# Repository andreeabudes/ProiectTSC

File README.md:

## Proiect InkTime

## Diagrama Bloc
Sistemul este organizat in jurul microcontroller-ului nRF52840, care gestioneaza comunicarea Bluetooth, procesarea datelor de la senzori si controlul afisajului.

## BOM (Bill Of Materials)
| Component | Part Number | Package | Function | Datasheet |
|---|---|---|---|---|
| MCU | nRF52840-QIAA-R | aQFN73 (7x7) | Microcontroller + BLE + USB | [Datasheet](https://docs.nordicsemi.com/) |
| Charger / Power Path | BQ25180YBGR | DSBGA-8 | Li-Ion/LiPo charger with power path | [Datasheet](https://www.ti.com/lit/ds/symlink/bq25180.pdf) |
| Buck-Boost Regulator | RT6160AWSC | WLCSP-15 | 3.3V system rail regulator | [Datasheet](https://www.richtek.com/assets/product_file/RT6160A/DS6160A-05.pdf) |
| Fuel Gauge | MAX17048G+T10 | DFN-8 (2x2) | Battery SOC monitoring | [Datasheet](https://www.analog.com/media/en/technical-documentation/data-sheets/MAX17048-MAX17049.pdf) |
| Accelerometer | BMA421 | LGA-12 (2x2) | Step counting + motion wake | [Datasheet](https://jlcpcb.com/partdetail/Bosch_Sensortec-BMA421/C5242966) |
| Haptic Driver | DRV2605LDGSR | VSSOP-10 | ERM motor driver with effects library | [Datasheet](https://www.ti.com/lit/ds/symlink/drv2605l.pdf) |
| PFET (EPD power) | SI2301CDS | SOT-23 | E-paper display power gating | [Datasheet](https://jlcpcb.com/partdetail/Changjiang_Electronics_Tech_CJ-SI2301CDS/C10487) |
| USB ESD Protection | USBLC6-2SC6Y | SOT-23-6 | ESD protection on USB data lines | [Datasheet](https://www.st.com/resource/en/datasheet/usblc6-2.pdf) |
| USB Type-C Connector | KH-TYPE-C-16P | 16-pin SMD | USB charging + data | [Datasheet](https://www.google.com/search?q=%23) |
 
> Toate rezistentele folosite sunt in capsula **0201**. Condensatoarele de bypass/decuplare de **100nF** sunt **0201**, iar cele care depasesc **100nF** sunt **0402**, conform constrangerilor de design.

## Functionalitate Hardware

### Module si Senzori

- **MCU – nRF52840:** Ales pentru consumul redus de energie si capabilitatile Bluetooth Low Energy (BLE). Acesta gestioneaza protocolul SPI pentru ecran, I2C pentru senzori si controleaza starea sistemului.

- **Display E-Paper:** Ofera o lizibilitate excelenta in lumina soarelui si consuma energie doar in momentul refresh-ului, fiind ideal pentru un smartwatch unde autonomia bateriei este critica.

- **Management Putere:** Sistem de power path si incarcare cu BQ25180YBGR, impreuna cu regulatorul Buck-Boost RT6160AWSC care asigura o tensiune stabila de 3.3V, indiferent de nivelul de descarcare al bateriei Li-Po. Monitorizarea precisa a bateriei (SOC) este realizata de integratul MAX17048G+T10.

- **Senzor Miscare:** Accelerometrul BMA421 este folosit pentru detectarea miscarii mainii (ex: "lift-to-wake" pentru a trezi ecranul din sleep) si pentru aplicatii de tip pedometru (step counting).

- **Feedback Haptic:** Motorul ERM este controlat precis de driverul DRV2605LDGSR, care include o librarie interna de efecte haptice.

---

### Specificatii Comunicatie

- **SPI (Display):** Interfata rapida pentru a asigura un refresh optim al ecranului (semnale MOSI, SCK, CS, DC).

- **I2C (Senzori & Power):** Folosita pentru comunicarea cu accelerometrul, fuel gauge-ul, charger-ul si driverul haptic.

- **SWD (Serial Wire Debug):** Interfata hardware standard de la ARM, conectata la un conector TC2030, folosita pentru incarcarea codului pe placa si pentru depanare pas cu pas a software-ului.

---

## Descriere pini nRF52840  

| Pin | Descriere |
|-----|----------|
| VDD | Alimentare 3V3 |
| DCC | Power regulation |
| DEC4 | Power regulation |
| VSS | GND |
| P0.02 / AIN0 | SPI SCK (clock pentru display) |
| P0.02 / AIN0 | SPI MOSI (master output slave in) |
| DEC2 | GND, power regulation |
| VDD | Alimentare 3V3 |
| XC2, XC1 | Oscilator X1 (32 MHz) |
| DEC3 | GND |
| DEC6 | Power regulation |
| VSS_PA | Alimentare antenă |
| ANT | Conectare antenă |
| P0.10 / NFC2 | Semnal alertă baterie (Fuel Gauge) |
| DEC5 | GND, power regulation |
| P1.02 | Buton Down |
| P1.01 | Control alimentare display |
| SWDIO, SWDCLK | Programare și debug |
| VDD | Alimentare 3V3 |
| VSS_PAD | GND |
| P1.00 | SWO (debug) |
| P0.18 / RESET | Pin Reset |
| P0.17, P0.16, P0.15 | Interfață display |
| P0.13, P0.14 | Butoane Enter / Up |
| D-, D+ | USB (transmisie diferențială) |
| VBUS | Alimentare USB 5V |
| DEC3V3 | GND (intern, power regulation) |
| DCCH | Nefolosit |
| VDDH, VDD | Alimentare 3V3 |
| P0.12 | Enable driver haptic |
| P0.11 | Alertă alimentare (de la LiPo Charger) |
| P1.08, P0.08 | Interrupții IMU |
| P0.07, P0.06 | I2C (SCL, SDA) |
| P0.05 / AIN3 | Chip Select display |
| XL2, XL1 | Oscilator X2 (32 kHz) |
| DEC1 | GND, power regulation |

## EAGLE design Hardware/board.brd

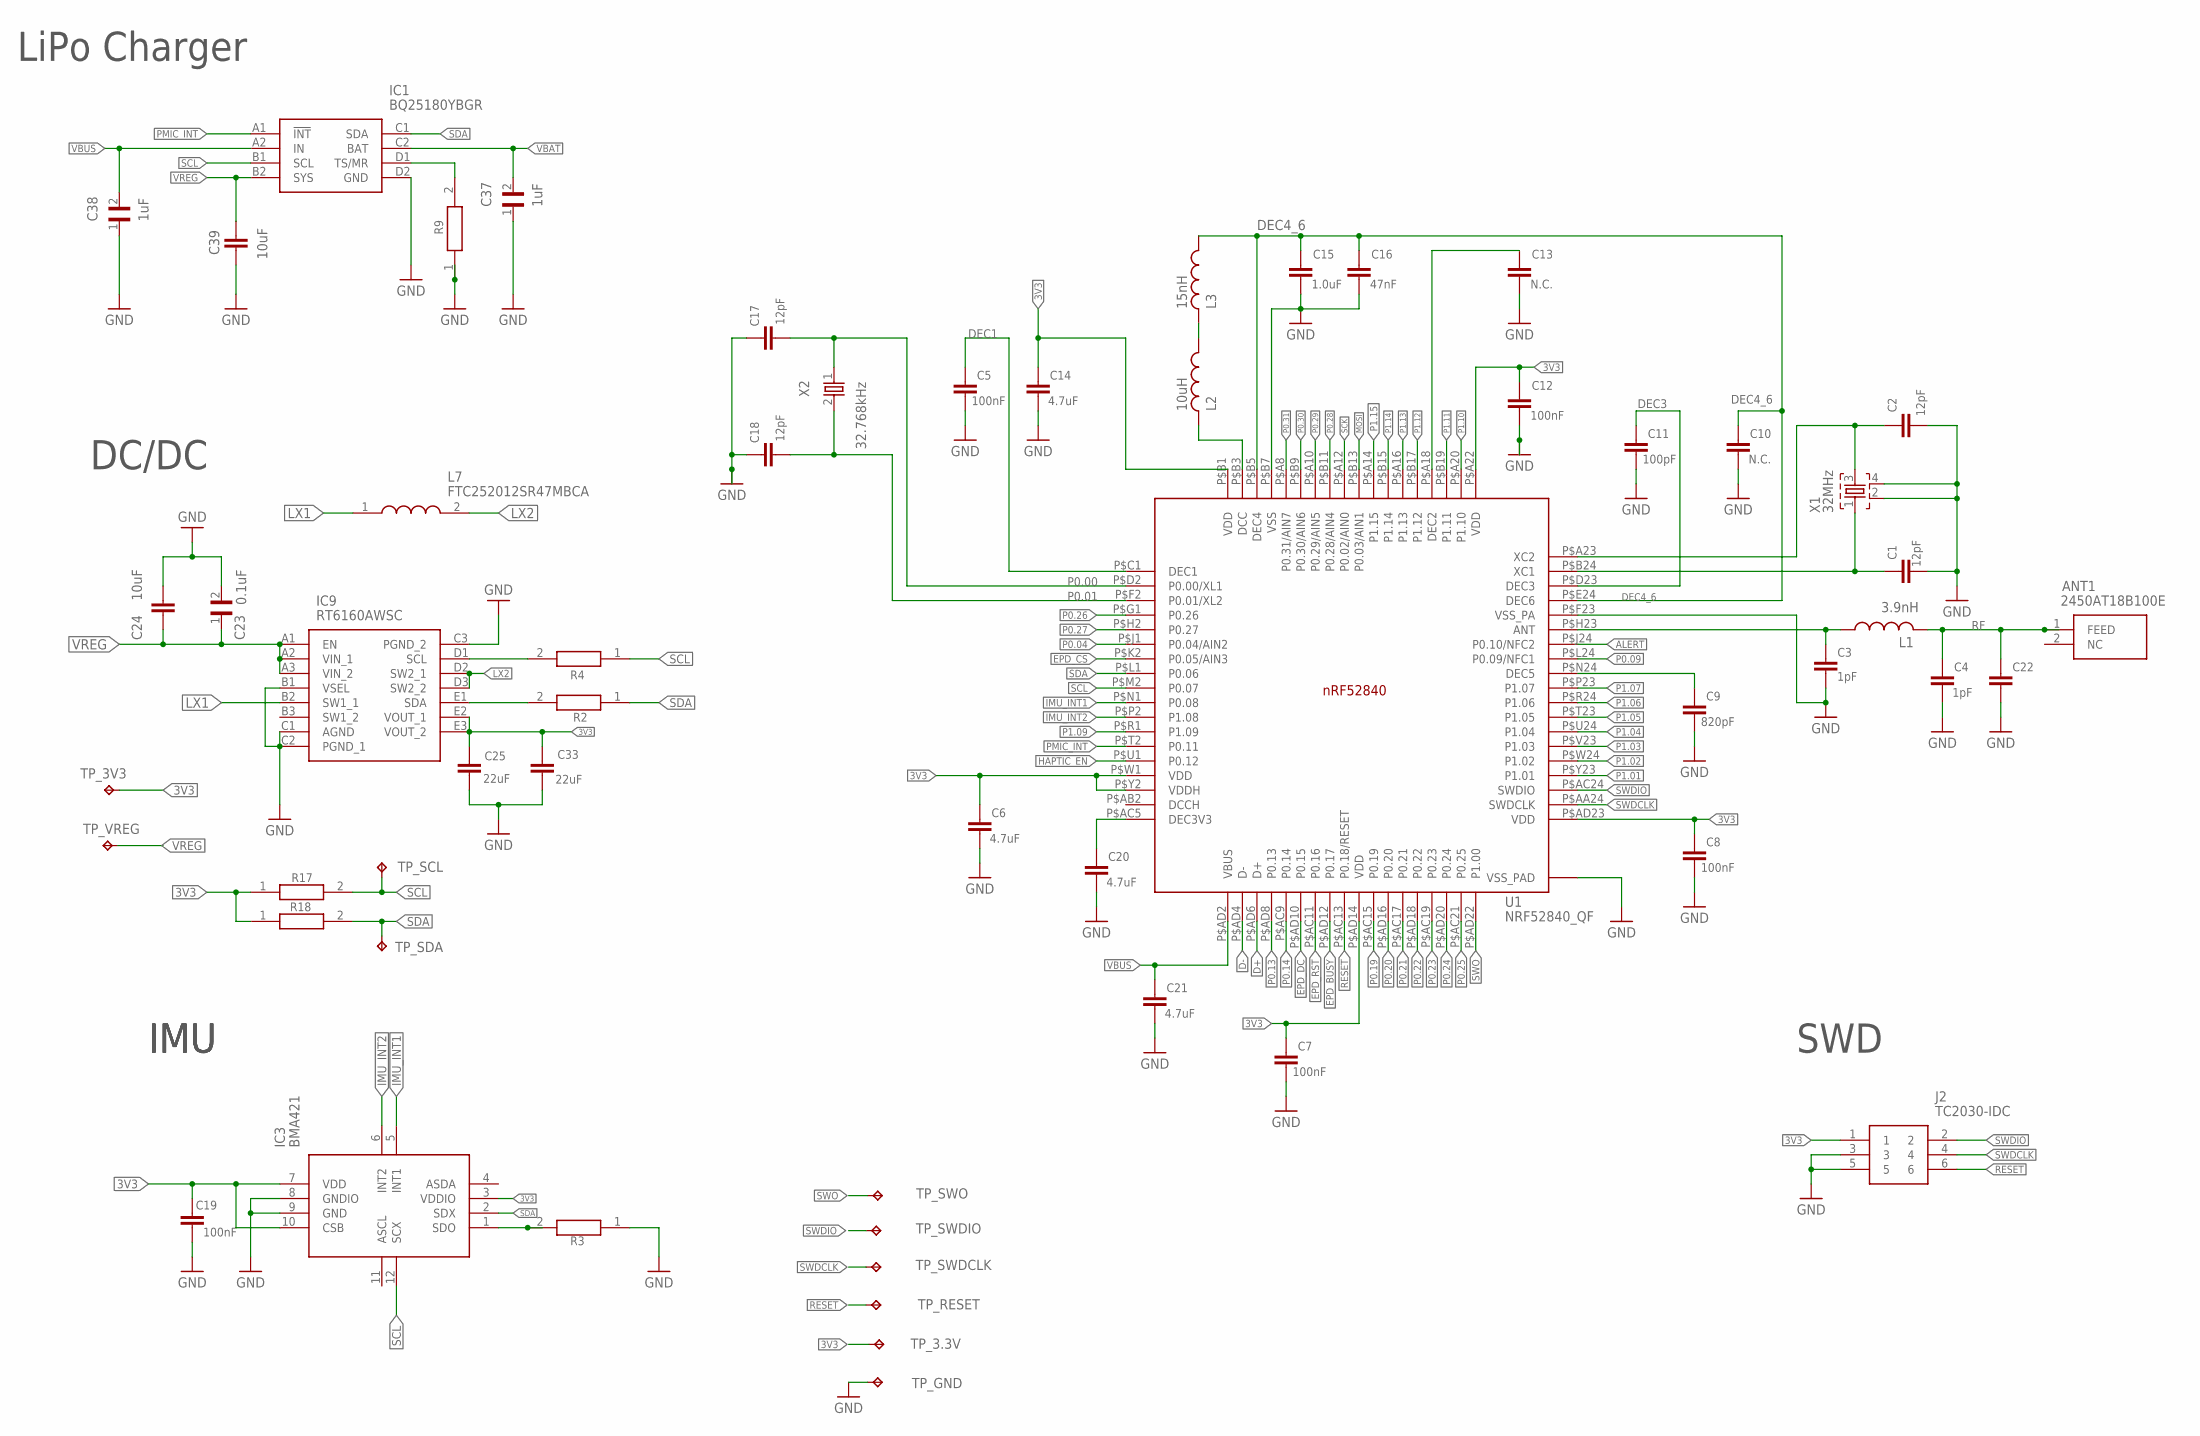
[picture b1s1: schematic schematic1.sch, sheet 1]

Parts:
ANT1: 2450AT18B100E; 2450AT18B100E_ANTC3216X140N
C1, C2, C17, C18: 12pF; ESP32_C6_LIBRARY_1_ESP32_WROVER_EAGLE-LTSPICE_C0402
C3, C4: 1pF; ESP32_C6_LIBRARY_1_ESP32_WROVER_EAGLE-LTSPICE_C0402
C5, C7, C8, C12, C19: 100nF; ESP32_C6_LIBRARY_1_ESP32_WROVER_EAGLE-LTSPICE_C0402
C6, C14, C20, C21: 4.7uF; ESP32_C6_LIBRARY_1_ESP32_WROVER_EAGLE-LTSPICE_C0402
C9: 820pF; ESP32_C6_LIBRARY_1_ESP32_WROVER_EAGLE-LTSPICE_C0402
C10, C13, C22: N.C.; ESP32_C6_LIBRARY_1_ESP32_WROVER_EAGLE-LTSPICE_C0402
C11: 100pF; ESP32_C6_LIBRARY_1_ESP32_WROVER_EAGLE-LTSPICE_C0402
C15: 1.0uF; ESP32_C6_LIBRARY_1_ESP32_WROVER_EAGLE-LTSPICE_C0402
C16: 47nF; ESP32_C6_LIBRARY_1_ESP32_WROVER_EAGLE-LTSPICE_C0402
C23: 0.1uF; GRM011R60J152KE01L_2_CAPC0201X13N
C24, C39: 10uF; ESP32_C6_LIBRARY_1_ESP32_WROVER_EAGLE-LTSPICE_C0402
C25, C33: 22uF; ESP32_C6_LIBRARY_1_ESP32_WROVER_EAGLE-LTSPICE_C0402
C37, C38: 1uF; GRM011R60J152KE01L_2_CAPC0201X13N
IC1: BQ25180YBGR; BQ25180YBGR_BGA8C40P2X4_100X155X50
IC3: BMA421; BMA423_BMA423
IC9: RT6160AWSC; RT6160AWSC_BGA15C40P3X5_140X230X60
J2: TC2030-IDC; TC2030-IDC_TC2030IDC
L1: 3.9nH; NORDIC_NRF_2_RESC0402_L
L2: 10uH; NORDIC_NRF_2_RESC0402_L
L3: 15nH; NORDIC_NRF_2_RESC0402_L
L7: FTC252012SR47MBCA; MLP2016SR47MT0S1_INDC2016X100N
R2, R3, R4: 0; ERA-1AEB3401C_0201
R9: 10K; ERA-1AEB3401C_0201
R17, R18: 3K3; ERA-1AEB3401C_0201
TP_3.3V, TP_3V3: HECTOR_WATCH_1_TPTP20R; HECTOR_WATCH_1_TP20R
TP_GND: HECTOR_WATCH_1_TPTP20R; HECTOR_WATCH_1_TP20R
TP_RESET: HECTOR_WATCH_1_TPTP20R; HECTOR_WATCH_1_TP20R
TP_SCL: HECTOR_WATCH_1_TPTP20R; HECTOR_WATCH_1_TP20R
TP_SDA: HECTOR_WATCH_1_TPTP20R; HECTOR_WATCH_1_TP20R
TP_SWDCLK: HECTOR_WATCH_1_TPTP20R; HECTOR_WATCH_1_TP20R
TP_SWDIO: HECTOR_WATCH_1_TPTP20R; HECTOR_WATCH_1_TP20R
TP_SWO: HECTOR_WATCH_1_TPTP20R; HECTOR_WATCH_1_TP20R
TP_VREG: HECTOR_WATCH_1_TPTP20R; HECTOR_WATCH_1_TP20R
U1: NRF52840_QF; NORDIC_NRF_4_AQFN50P700X700X85_HS-74N
X1: 32MHz; NORDIC_NRF_BT-XTAL_2016_N
X2: 32.768kHz; NORDIC_NRF_1_XTAL_3215_N

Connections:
3V3: C6.2, C7.2, C8.2, C12.1, C14.2, C19.1, C25.1, C33.1, IC3.3 (VDDIO), IC3.7 (VDD), IC3.10 (CSB), IC9.E2 (VOUT_1), IC9.E3 (VOUT_2), J2.1, R17.1, R18.1, TP_3.3V.TP, TP_3V3.TP, U1.P$A22 (VDD), U1.P$AD14 (VDD), U1.P$AD23 (VDD), U1.P$B1 (VDD), U1.P$W1 (VDD), U1.P$Y2 (VDDH); also elsewhere on the board
ALERT: U1.P$J24 (P0.10/NFC2); also elsewhere on the board
D+: U1.P$AD6 (D+); also elsewhere on the board
D-: U1.P$AD4 (D-); also elsewhere on the board
DEC1: C5.2, U1.P$C1 (DEC1)
DEC3: C11.2, U1.P$D23 (DEC3)
DEC4_6: C10.2, C15.1, C16.1, L3.1, U1.P$B5 (DEC4), U1.P$E24 (DEC6)
EPD_BUSY: U1.P$AD12 (P0.17); also elsewhere on the board
EPD_CS: U1.P$K2 (P0.05/AIN3); also elsewhere on the board
EPD_DC: U1.P$AD10 (P0.15); also elsewhere on the board
EPD_RST: U1.P$AC11 (P0.16); also elsewhere on the board
GND: C1.1, C2.2, C3.1, C4.1, C5.1, C6.1, C7.1, C8.1, C9.1, C10.1, C11.1, C12.2, C13.2, C14.1, C15.2, C16.2, C17.2, C18.2, C19.2, C20.1, C21.1, C22.1, C23.2, C24.1, C25.2, C33.2, C37.1, C38.1, C39.2, IC1.D2 (GND), IC3.8 (GNDIO), IC3.9 (GND), IC9.B1 (VSEL), IC9.C1 (AGND), IC9.C2 (PGND_1), IC9.C3 (PGND_2), J2.3, J2.5, R3.1, R9.1, TP_GND.TP, U1.P$74 (VSS_PAD), U1.P$75 (VSS_PAD), U1.P$76 (VSS_PAD), U1.P$77 (VSS_PAD), U1.P$78 (VSS_PAD), U1.P$79 (VSS_PAD), U1.P$80 (VSS_PAD), U1.P$81 (VSS_PAD), U1.P$82 (VSS_PAD), U1.P$83 (VSS_PAD), U1.P$84 (VSS_PAD), U1.P$85 (VSS_PAD), U1.P$86 (VSS_PAD), U1.P$87 (VSS_PAD), U1.P$88 (VSS_PAD), U1.P$89 (VSS_PAD), U1.P$90 (VSS_PAD), U1.P$B7 (VSS), U1.P$F23 (VSS_PA), X1.2, X1.4; also elsewhere on the board
HAPTIC_EN: U1.P$U1 (P0.12); also elsewhere on the board
IMU_INT1: IC3.5 (INT1), U1.P$N1 (P0.08)
IMU_INT2: IC3.6 (INT2), U1.P$P2 (P1.08)
LX1: IC9.B2 (SW1_1), L7.1
LX2: IC9.D2 (SW2_1), IC9.D3 (SW2_2), L7.2
MOSI: U1.P$B13 (P0.03/AIN1); also elsewhere on the board
unnamed: C9.2, U1.P$N24 (DEC5)
unnamed: L2.2, U1.P$B3 (DCC)
unnamed: IC1.D1 (TS/MR), R9.2
unnamed: IC9.D1 (SCL), R4.2
unnamed: C1.2, U1.P$B24 (XC1), X1.1
unnamed: IC9.E1 (SDA), R2.2
unnamed: C13.1, U1.P$A18 (DEC2)
unnamed: C3.2, L1.2, U1.P$H23 (ANT)
unnamed: C2.1, U1.P$A23 (XC2), X1.3
unnamed: IC3.1 (SDO), R3.2
unnamed: L2.1, L3.2
unnamed: C20.2, U1.P$AC5 (DEC3V3)
P0.00: C17.1, U1.P$D2 (P0.00/XL1), X2.1
P0.01: C18.1, U1.P$F2 (P0.01/XL2), X2.2
P0.04: U1.P$J1 (P0.04/AIN2)
P0.09: U1.P$L24 (P0.09/NFC1)
P0.13: U1.P$AD8 (P0.13); also elsewhere on the board
P0.14: U1.P$AC9 (P0.14); also elsewhere on the board
P0.19: U1.P$AC15 (P0.19)
P0.20: U1.P$AD16 (P0.20)
P0.21: U1.P$AC17 (P0.21)
P0.22: U1.P$AD18 (P0.22)
P0.23: U1.P$AC19 (P0.23)
P0.24: U1.P$AD20 (P0.24)
P0.25: U1.P$AC21 (P0.25)
P0.26: U1.P$G1 (P0.26)
P0.27: U1.P$H2 (P0.27)
P0.28: U1.P$B11 (P0.28/AIN4)
P0.29: U1.P$A10 (P0.29/AIN5)
P0.30: U1.P$B9 (P0.30/AIN6)
P0.31: U1.P$A8 (P0.31/AIN7)
P1.01: U1.P$Y23 (P1.01); also elsewhere on the board
P1.02: U1.P$W24 (P1.02); also elsewhere on the board
P1.03: U1.P$V23 (P1.03)
P1.04: U1.P$U24 (P1.04)
P1.05: U1.P$T23 (P1.05)
P1.06: U1.P$R24 (P1.06)
P1.07: U1.P$P23 (P1.07)
P1.09: U1.P$R1 (P1.09)
P1.10: U1.P$A20 (P1.10)
P1.11: U1.P$B19 (P1.11)
P1.12: U1.P$B17 (P1.12)
P1.13: U1.P$A16 (P1.13)
P1.14: U1.P$B15 (P1.14)
P1.15: U1.P$A14 (P1.15)
PMIC_INT: IC1.A1 (!INT), U1.P$T2 (P0.11)
RESET: J2.6, TP_RESET.TP, U1.P$AC13 (P0.18/RESET)
RF: ANT1.1 (FEED), C4.2, C22.2, L1.1
SCK: U1.P$A12 (P0.02/AIN0); also elsewhere on the board
SCL: IC1.B1 (SCL), IC3.12 (SCX), R4.1, R17.2, TP_SCL.TP, U1.P$M2 (P0.07); also elsewhere on the board
SDA: IC1.C1 (SDA), IC3.2 (SDX), R2.1, R18.2, TP_SDA.TP, U1.P$L1 (P0.06); also elsewhere on the board
SWDCLK: J2.4, TP_SWDCLK.TP, U1.P$AA24 (SWDCLK)
SWDIO: J2.2, TP_SWDIO.TP, U1.P$AC24 (SWDIO)
SWO: TP_SWO.TP, U1.P$AD22 (P1.00)
VBAT: C37.2, IC1.C2 (BAT); also elsewhere on the board
VBUS: C21.2, C38.2, IC1.A2 (IN), U1.P$AD2 (VBUS); also elsewhere on the board
VREG: C23.1, C24.2, C39.1, IC1.B2 (SYS), IC9.A1 (EN), IC9.A2 (VIN_1), IC9.A3 (VIN_2), TP_VREG.TP

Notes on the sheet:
LiPo Charger
DC/DC
IMU
SWD

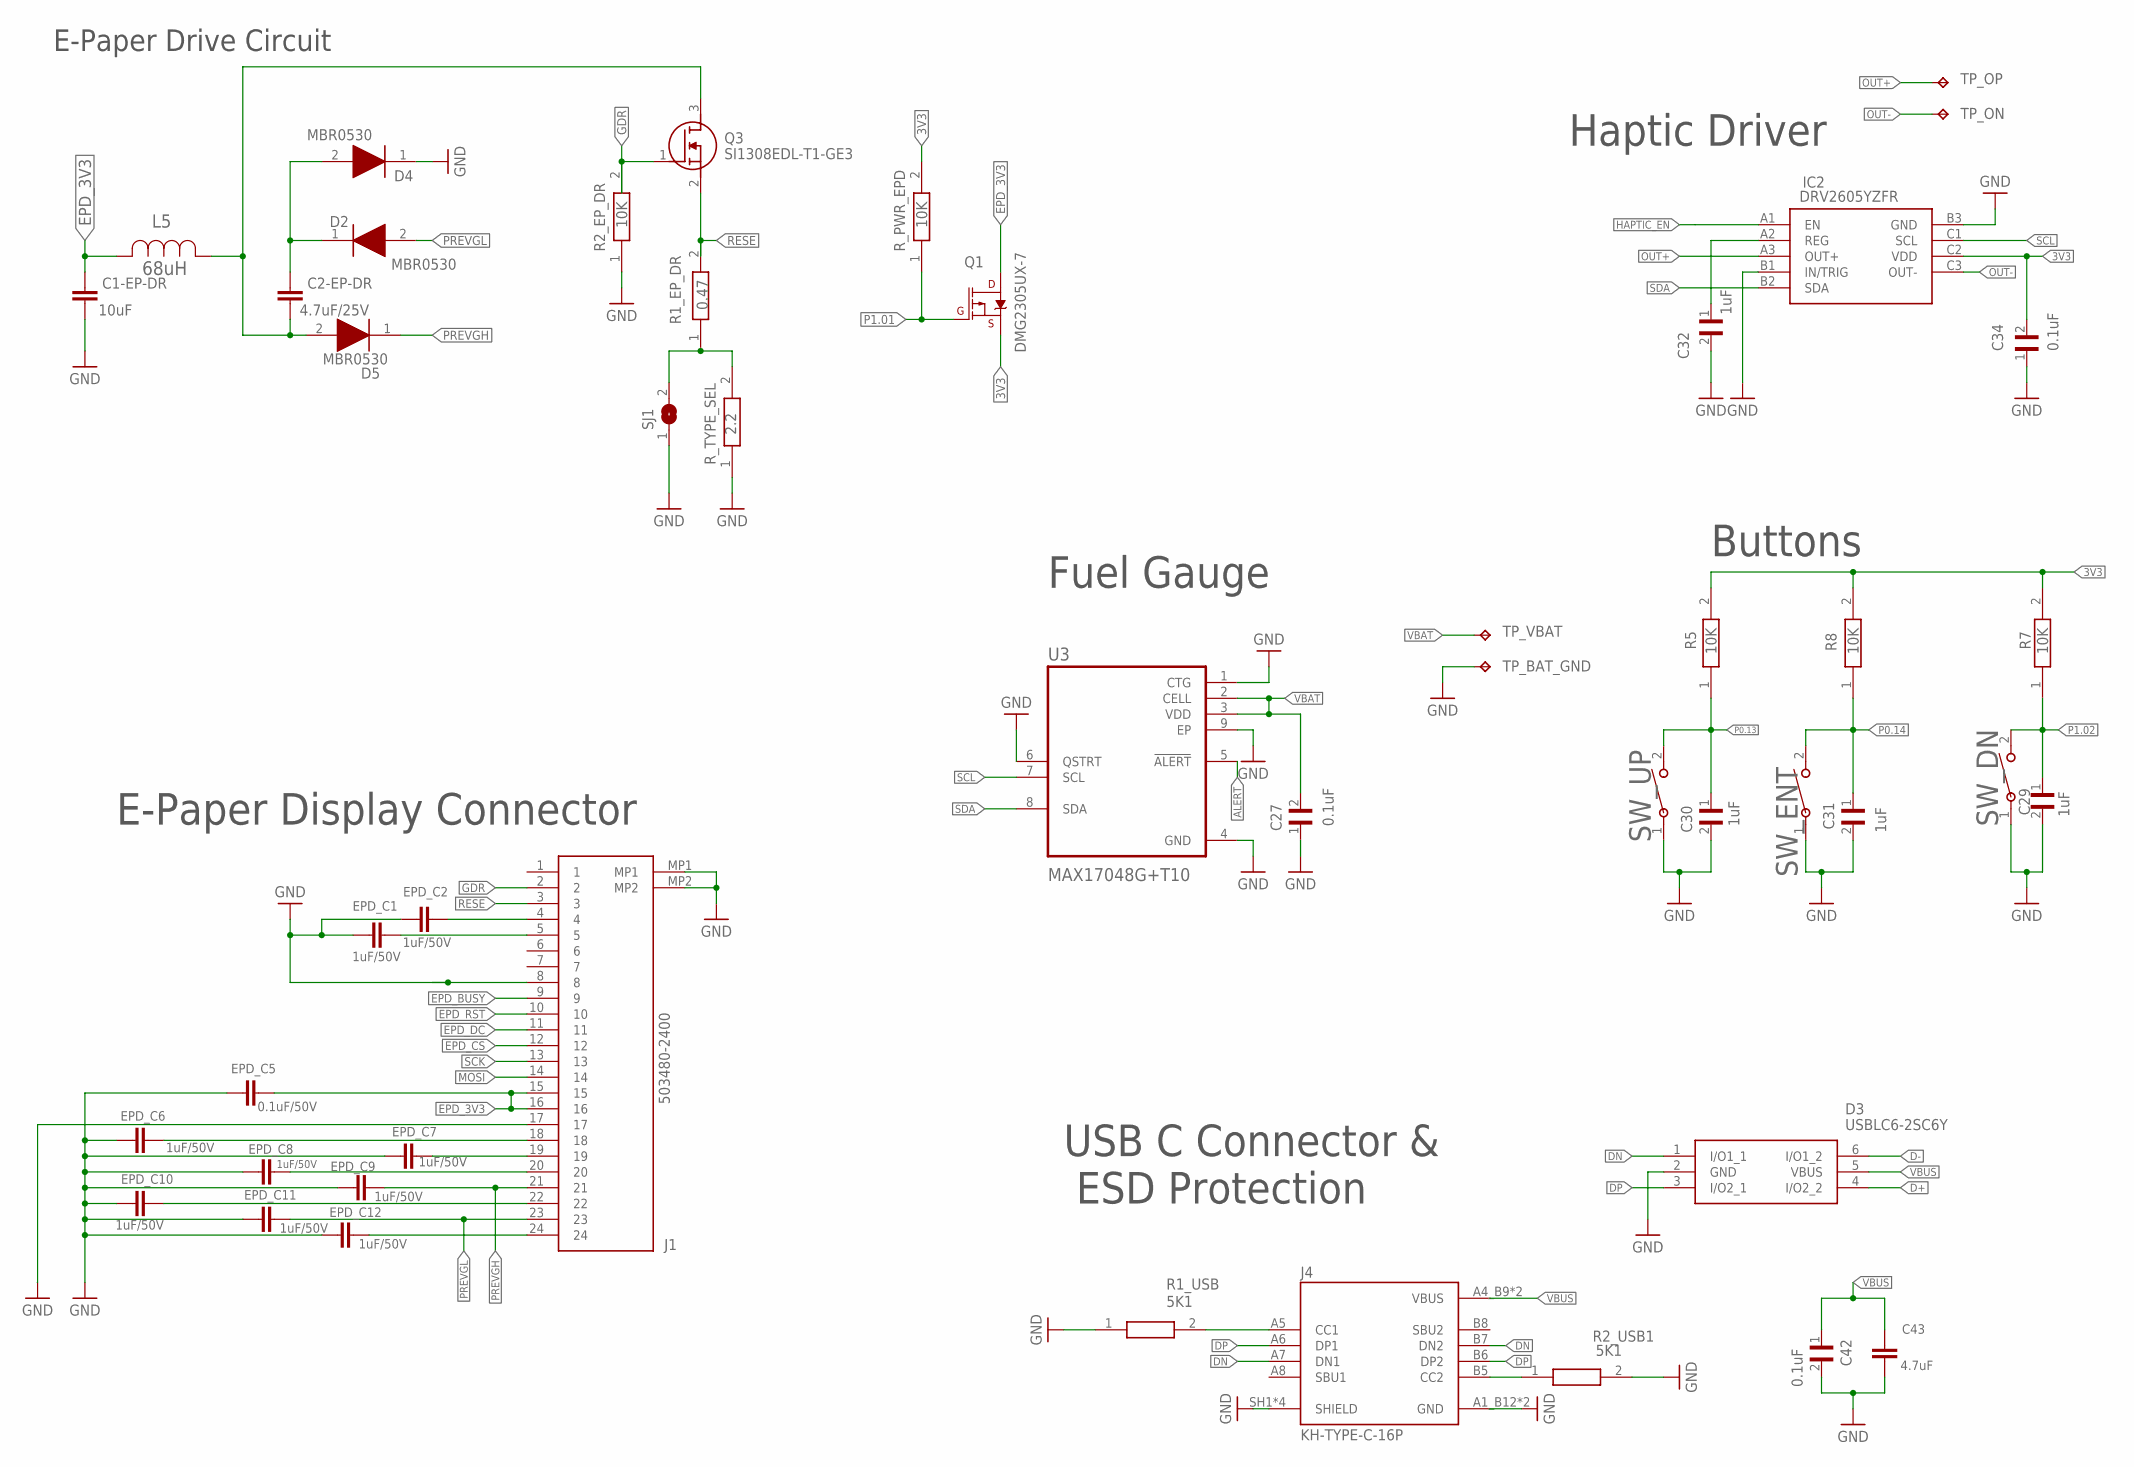
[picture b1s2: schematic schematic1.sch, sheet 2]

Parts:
C1-EP-DR: 10uF; ESP32_C6_LIBRARY_1_ESP32_WROVER_EAGLE-LTSPICE_C0402
C2-EP-DR: 4.7uF/25V; ESP32_C6_LIBRARY_1_ESP32_WROVER_EAGLE-LTSPICE_C0402
C27, C34, C42: 0.1uF; GRM011R60J152KE01L_2_CAPC0201X13N
C29, C30, C31, C32: 1uF; GRM011R60J152KE01L_2_CAPC0201X13N
C43: 4.7uF; ESP32_C6_LIBRARY_1_ESP32_WROVER_EAGLE-LTSPICE_C0402
D2, D4, D5: MBR0530; ESP32_C6_LIBRARY_5_SOD3716X135N
D3: USBLC6-2SC6Y; ESP32_C6_LIBRARY_3_SOT95P280X145-6N
EPD_C1, EPD_C2, EPD_C6, EPD_C7, EPD_C8, EPD_C9, EPD_C10, EPD_C11, EPD_C12: 1uF/50V; ESP32_C6_LIBRARY_1_ESP32_WROVER_EAGLE-LTSPICE_C0402
EPD_C5: 0.1uF/50V; ESP32_C6_LIBRARY_1_ESP32_WROVER_EAGLE-LTSPICE_C0402
IC2: DRV2605YZFR; DRV2605YZFR_BGA9C50P3X3_144X144X62
J1: 503480-2400; 503480-2400_5034802400
J4: KH-TYPE-C-16P; KH-TYPE-C-16P_KINGHELM_KH-TYPE-C-16P
L5: 68uH; ESP32_C6_LIBRARY_2_IND_4828-WE-TPC_WRE
Q1: DMG2305UX-7; ESP32_C6_LIBRARY_4_ESP32_C6_LIBRARY_4_ESP32_C6_LIBRARY_4_ES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
Q3: SI1308EDL-T1-GE3; ESP32_C6_LIBRARY_6_SOT65P210X110-3N
R1_EP_DR: 0.47; ERA-1AEB3401C_0201
R1_USB, R2_USB1: 5K1; ERA-1AEB3401C_0201
R2_EP_DR, R5, R7, R8: 10K; ERA-1AEB3401C_0201
R_PWR_EPD: 10K; ERA-1AEB3401C_0201
R_TYPE_SEL: 2.2; ERA-1AEB3401C_0201
SJ1: ESP32_C6_LIBRARY_7_JUMPER_SJ
SW_DN: 2025-10-22_07-23-44_LIBRARY_EVP-AKE31ASW_EVP-AKE3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; 2025-10-22_07-23-44_LIBRARY_SW_EVP-AKE31A_PAN
SW_ENT: 2025-10-22_07-23-44_LIBRARY_EVP-AKE31ASW_EVP-AKE3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; 2025-10-22_07-23-44_LIBRARY_SW_EVP-AKE31A_PAN
SW_UP: 2025-10-22_07-23-44_LIBRARY_EVP-AKE31ASW_EVP-AKE3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; 2025-10-22_07-23-44_LIBRARY_SW_EVP-AKE31A_PAN
TP_BAT_GND: HECTOR_WATCH_1_TPTP20R; HECTOR_WATCH_1_TP20R
TP_ON: HECTOR_WATCH_1_TPTP20R; HECTOR_WATCH_1_TP20R
TP_OP: HECTOR_WATCH_1_TPTP20R; HECTOR_WATCH_1_TP20R
TP_VBAT: HECTOR_WATCH_1_TPTP20R; HECTOR_WATCH_1_TP20R
U3: MAX17048G+T10; ESP32_C6_LIBRARY_SON50P200X200X80-9N

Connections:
3V3: C34.2, IC2.C2 (VDD), Q1.2 (S), R5.2, R7.2, R8.2, R_PWR_EPD.2; also elsewhere on the board
ALERT: U3.5 (!ALERT); also elsewhere on the board
D+: D3.4 (I/O2_2); also elsewhere on the board
D-: D3.6 (I/O1_2); also elsewhere on the board
DN: D3.1 (I/O1_1), J4.A7 (DN1), J4.B7 (DN2)
DP: D3.3 (I/O2_1), J4.A6 (DP1), J4.B6 (DP2)
EPD_3V3: C1-EP-DR.2, EPD_C5.2, J1.15, J1.16, L5.2, Q1.3 (D)
EPD_BUSY: J1.9; also elsewhere on the board
EPD_CS: J1.12; also elsewhere on the board
EPD_DC: J1.11; also elsewhere on the board
EPD_RST: J1.10; also elsewhere on the board
GDR: J1.2, Q3.1 (G), R2_EP_DR.2
GND: C1-EP-DR.1, C27.1, C29.2, C30.2, C31.2, C32.2, C34.1, C42.2, C43.1, D3.2 (GND), D4.1 (K), EPD_C1.1, EPD_C2.1, EPD_C5.1, EPD_C6.1, EPD_C7.1, EPD_C8.1, EPD_C9.1, EPD_C10.1, EPD_C11.1, EPD_C12.1, IC2.B1 (IN/TRIG), IC2.B3 (GND), J1.8, J1.17, J1.MP1, J1.MP2, J4.A1_B12 (GND), J4.A12_B1 (GND), J4.SH1 (SHIELD), J4.SH2 (SHIELD), J4.SH3 (SHIELD), J4.SH4 (SHIELD), R1_USB.1, R2_EP_DR.1, R2_USB1.2, R_TYPE_SEL.1, SJ1.1, SW_DN.1, SW_ENT.1, SW_UP.1, TP_BAT_GND.TP, U3.1 (CTG), U3.4 (GND), U3.6 (QSTRT), U3.9 (EP); also elsewhere on the board
HAPTIC_EN: IC2.A1 (EN); also elsewhere on the board
MOSI: J1.14; also elsewhere on the board
unnamed: C2-EP-DR.2, D2.1 (K), D4.2 (A)
unnamed: C2-EP-DR.1, D5.2 (A), L5.1, Q3.3 (D)
unnamed: R1_EP_DR.1, R_TYPE_SEL.2, SJ1.2
unnamed: EPD_C2.2, J1.4
unnamed: EPD_C1.2, J1.5
unnamed: EPD_C6.2, J1.18
unnamed: EPD_C7.2, J1.19
unnamed: EPD_C8.2, J1.20
unnamed: EPD_C10.2, J1.22
unnamed: J4.B5 (CC2), R2_USB1.1
unnamed: EPD_C12.2, J1.24
unnamed: C32.1, IC2.A2 (REG)
unnamed: J4.A5 (CC1), R1_USB.2
OUT+: IC2.A3 (OUT+), TP_OP.TP
OUT-: IC2.C3 (OUT-), TP_ON.TP
P0.13: C30.1, R5.1, SW_UP.2; also elsewhere on the board
P0.14: C31.1, R8.1, SW_ENT.2; also elsewhere on the board
P1.01: Q1.1 (G), R_PWR_EPD.1; also elsewhere on the board
P1.02: C29.1, R7.1, SW_DN.2; also elsewhere on the board
PREVGH: D5.1 (K), EPD_C9.2, J1.21
PREVGL: D2.2 (A), EPD_C11.2, J1.23
RESE: J1.3, Q3.2 (S), R1_EP_DR.2
SCK: J1.13; also elsewhere on the board
SCL: IC2.C1 (SCL), U3.7 (SCL); also elsewhere on the board
SDA: IC2.B2 (SDA), U3.8 (SDA); also elsewhere on the board
VBAT: C27.2, TP_VBAT.TP, U3.2 (CELL), U3.3 (VDD); also elsewhere on the board
VBUS: C42.1, C43.2, D3.5 (VBUS), J4.A4_B9 (VBUS), J4.A9_B4 (VBUS); also elsewhere on the board

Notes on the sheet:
E-Paper Drive Circuit
E-Paper Display Connector
Haptic Driver
Buttons
USB C Connector & ESD Protection
Fuel Gauge

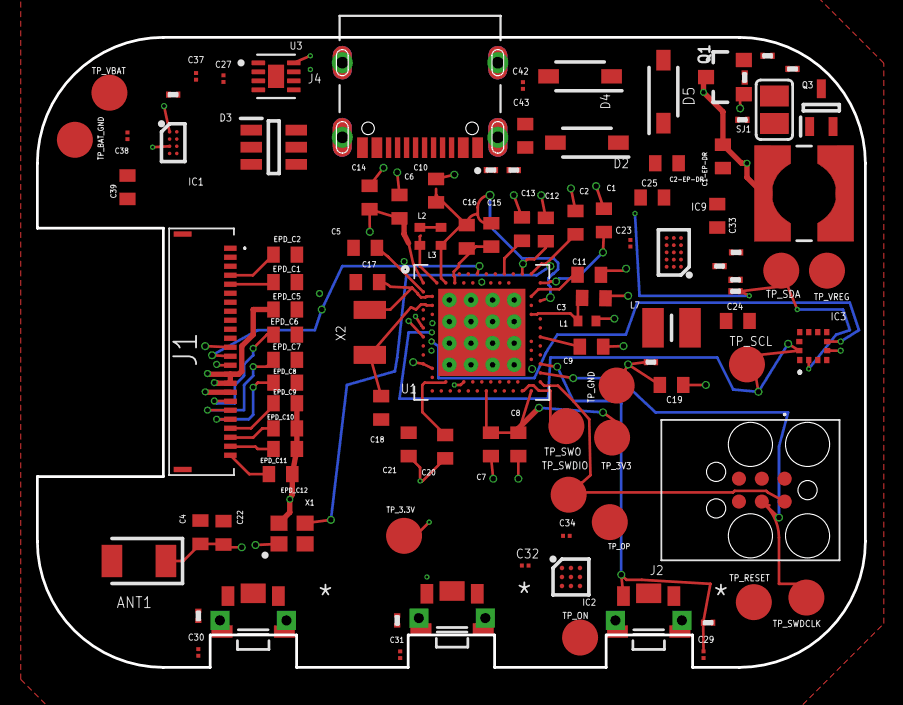
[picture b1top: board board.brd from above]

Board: 2 copper layers, 46.0 x 35.0 mm, 105 parts (0 on the bottom side), 70 nets.

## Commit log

2026-04-10 Am adaugat schematicul fara erori
2026-04-10 Create LICENSE
2026-04-10 inceput board
2026-04-17 add review
2026-04-17 add review
    Updated review.md to improve clarity and organization of sections.
2026-04-19 schematic corectat + board
2026-04-19 adaugare readme
2026-04-19 adaugat bom + pick and place
2026-04-20 adaugat gerbers
2026-04-20 imagini

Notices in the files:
parts and their libraries:
COPYRIGHT: Copyright (C) 2024 Ultra Librarian. All rights reserved.
COPYRIGHT: Copyright (C) 2025 Ultra Librarian. All rights reserved.
